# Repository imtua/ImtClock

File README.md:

# ImtClock - Blare

**ImtClock** is a project made for <a href="stardance.hackclub.com"><b>Stardance</b></a> from <a href="hackclub.com"><b>Hack Club</b></a>. ImtClock is a reference/example product of <a href="https://blare.hackclub.com"><b>Blare</b></a>, being funded by them too.

## Schematics

## Footprints 

## PCB

## 3D Overview of the PCB

## Parts of ImtClock

## Result

## Ingredients needed to make this
- 1x <a href="https://wiki.seeedstudio.com/XIAO_ESP32C3_Getting_Started/"><b>Seeed Studio XIAO ESP32-C3</b></a>
- 4x <a href="https://cdn.shopify.com/s/files/1/0565/8070/2297/files/SPEC-KS-3Y10B050NW-X1-Yellow_Switch.pdf?v=1675841028"><b>MX Style Keyboard Switches</b></a>
- 4x White Blank DSA Keycaps
- 1x 2.25in TFT Screen
- 1x 3.3V Piezo Buzzer

## Things Hack Club will provide
**Items:**
- 1x <a href="https://wiki.seeedstudio.com/XIAO_ESP32C3_Getting_Started/"><b>Seeed XIAO ESP32C3</b></a>
- 12x -<a href="https://cdn.shopify.com/s/files/1/0565/8070/2297/files/SPEC-KS-3Y10B050NW-X1-Yellow_Switch.pdf?v=1675841028"><b>MX-Style Keyboard Switches</b></a>
- 12x <a href="https://www.kromekeycaps.com/products/single-blank-dsa-pbt-keycaps?variant=55689072443774"><b>White Blank DSA Keycaps</b></a>
- 12x <a href="https://www.vishay.com/docs/81857/1n4148.pdf"><b>Through-Hole 1N4148 Diodes</b></a>
- 1x <a href="https://www.buydisplay.com/2-25-inch-tft-serial-spi-76x284-lcd-display-module-w-st7789p3"><b>2.25in TFT Screen</b></a>
- 1x <a href="https://store.roboticsbd.com/audio-voice-piezo-buzzer-speech-module/2301-active-buzzer-module-robotics-bangladesh.html"><b>3.3V Piezo Buzzer</b></a>
- 1x 2.54mm 8 Pin Male Header
- 8x 20cm Female-Female Jumper Wires
- 8x <a href="https://www.aliexpress.com/item/4000232858343.html?gatewayAdapt=usa2glo4itemAdapt"><b>M3x5x4 Heatset Inserts
- 4x M3x8mm Screws
- 4x M3x16mm Screws

**Grants:**
- **10$** Grant for **Blare PCB**
- **8$** Grant for **Blare 3D Print**
- **18$** Grant for a **soldering iron**, if you need one!

**Hack Club** will provide their <a href="https://blare.hackclub.com/docs/rewards/"><b>Blare Kit</b></a> for this project. Here is an image to convey items they'll provide-

## Thanks to Hack Club
Made by <a href="github.com/imtua"><b>Imtiaz Ahamed</b></a> with the help of <a href="hackclub.com"><b>Hack Club</b></a>.

Hack Club Stardance: https://stardance.hackclub.com/

Register through my link: <a href="https://stardance.space/7-aq7c7"><b>Register now!</b></a>

ImtClock project on Stardance: <a href="stardance.hackclub.com/projects/56342"><b>ImtClock</b></a>

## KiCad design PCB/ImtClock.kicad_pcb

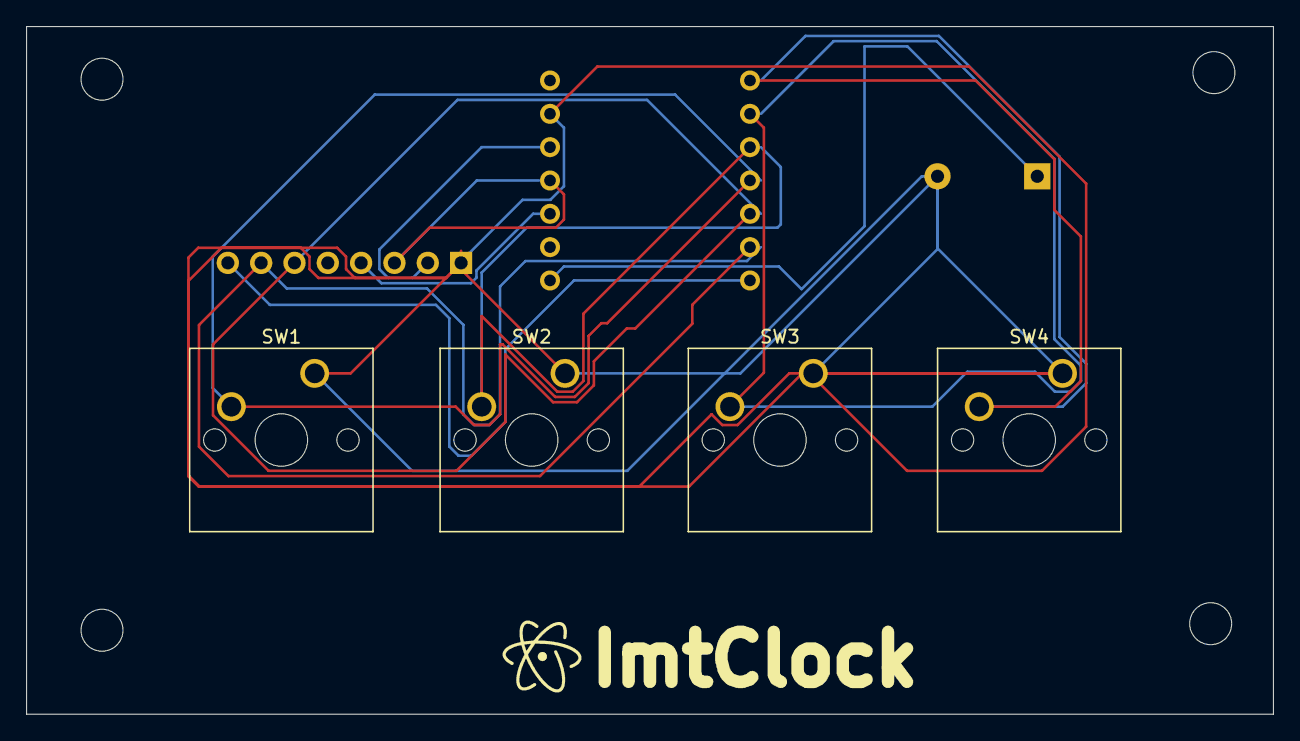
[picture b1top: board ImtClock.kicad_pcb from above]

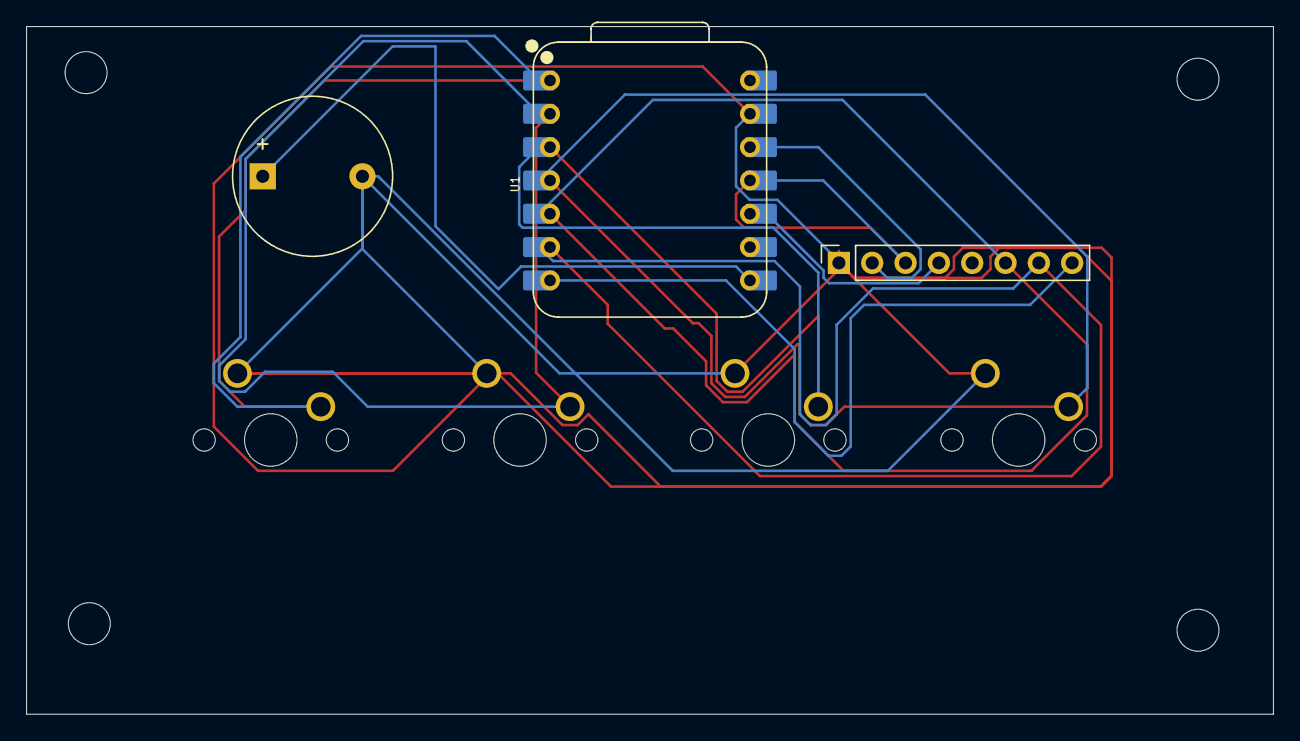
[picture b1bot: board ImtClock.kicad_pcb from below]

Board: 2 copper layers, 95.0 x 52.4 mm, 11 parts (3 on the bottom side), 12 nets.

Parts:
BZ1: Buzzer; Buzzer_12x9.5RM7.6
H1, H2, H3, H4: MountingHole; MountingHole_3.2mm_M3
J1: Conn_01x08_Pin; PinSocket_1x08_P2.54mm_Vertical
SW1, SW2, SW3, SW4: SW_Push; SW_Cherry_MX_1.00u_PCB
U1: XIAO-ESP32-C3-SMD; XIAO-ESP32-C3-DIP

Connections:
+3.3V: J1.2, U1.12 (3V3_OUT)
/BL: J1.8, U1.7 (D6)
/CS: J1.7, U1.6 (D5)
/DC: J1.6, U1.5 (D4)
/SCL: J1.4, U1.10 (D9/BOOT)
/SDA: J1.3, U1.11 (D10)
GND: BZ1.2 (-), J1.1, SW1.1, SW2.1, SW3.1, SW4.1, U1.13 (GND)
unnamed: BZ1.1 (+), U1.8 (D7)
unnamed: SW4.2, U1.1 (D0)
unnamed: SW3.2, U1.2 (D1)
unnamed: SW2.2, U1.3 (D2)
unnamed: SW1.2, U1.4 (D3)
